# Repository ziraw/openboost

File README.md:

# Open Source Boost Controller w/ ESP32-C3 SuperMini.  
This is REV2.0 fixing the mistakes of my previous PCB design, it's currently not field tested. 

**The Code was mainly written by an LLM, since I'm extremely inexperienced with coding, please be advised that this is not in any way "safe" to hook up to your engine, please take a minute and review the code yourself and decide for yourself. If you find anything that you might want to change I'm more than happy to see a PR opened!**  
speaking of code, the 2 LEDs are currently not in use.

I'm grabbing the MAP signal off of my gauge atm, which seems to work perfectly fine. You can theoretically hook up a separate sensor to the board itself if you want, although I would never ever use any sort of boost controller without an actual gauge!  

### I/O
It has a 5V output and a sensor passthrough on the JST connector, alongside the main I/O;  
1 - 12V  
2 - GND  
3 - SENS I/O  
4 - SENS I/O  
5 - 5V  
6 - VALVE  

The controller sits between the Valves GND connection and the Chassis to switch it at ~28hz via a PWM signal generated by a PID controller running on the ESP32.
To set Parameters (PID and Boost) it runs a Webserver on it's own WIFI network, which is kind of tedious, but I might add physical controls too a future version, for now the aim of this project is to keep it as **cheap and accessible as possible.**

### BOM (THT unless Specified):
- ESP32-C3 SuperMini  
- IRLZ44N  
- TC4422  
- TIP2955  
- L7805  
- 6P JST-VH Horizontal Connector  
- 2x SMD 2020 WS2812B (not used in Code atm)  
- Various Resistors  
- 2x220uF 16V  
- 3x100nF Ceramic  
- 1N4007 Diode (at Boost Valve)  
- (Pin Sockets for ESP32)

Valve used at Wastegate: BMW N75 Boost Control Valve (on a CA18DET Engine), although any suitable boost/mac valve should be fine to use. You have to hook up above mentioned flyback diode directly to the pins of the valve.

Link to my original reddit post from rev 1: https://www.reddit.com/r/esp32/comments/1vrntt0/i_made_a_boost_controller_with_a_esp32c3_first/

### Schematics

Feel free to DM me on reddit: /u/ziraw_tech

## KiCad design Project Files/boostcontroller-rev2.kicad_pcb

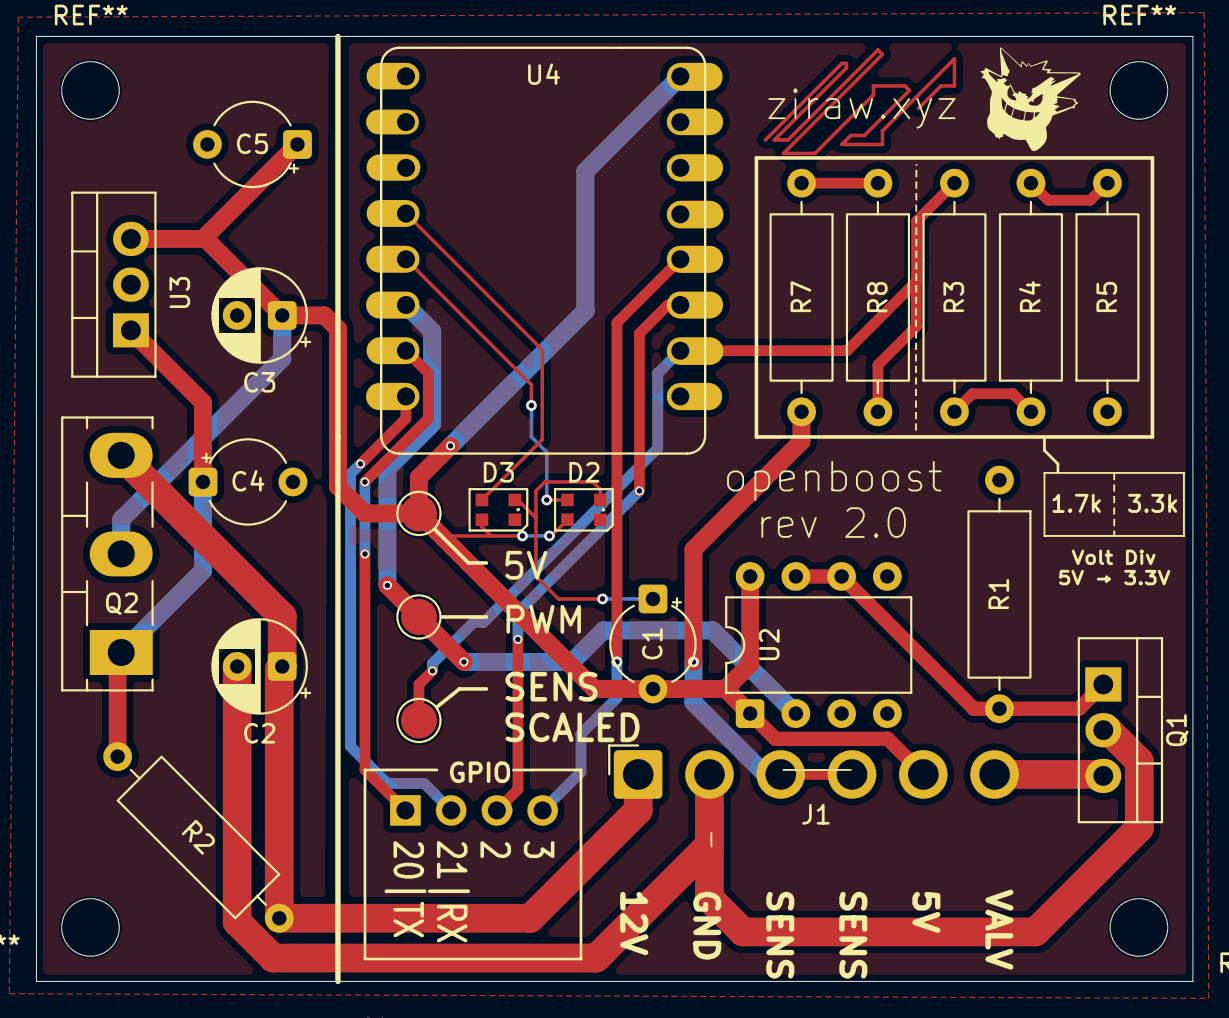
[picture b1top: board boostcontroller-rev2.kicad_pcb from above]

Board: 2 copper layers, 64.2 x 52.5 mm, 24 parts (0 on the bottom side), 18 nets.

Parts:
C1: Ceramic 100nF; CP_Radial_Tantal_D4.5mm_P5.00mm
C2, C3: 220uF 16V; CP_Radial_D5.0mm_P2.50mm
C4, C5: C 0.1uF; CP_Radial_Tantal_D4.5mm_P5.00mm
D2, D3: WS2812B; LED_WS2812B-2020_PLCC4_2.0x2.0mm
J1: Conn_01x06_Pin; JST_VH_B6PS-VH_1x06_P3.96mm_Horizontal
J2: Conn_01x04_Pin; PinHeader_1x04_P2.54mm_Vertical
Q1: IRLZ44N; TO-220-3_Vertical
Q2: TIP2955; TO-218-3_Vertical
R1: R10k; R_Axial_DIN0309_L9.0mm_D3.2mm_P12.70mm_Horizontal
R2: R3.3Ohm; R_Axial_DIN0309_L9.0mm_D3.2mm_P12.70mm_Horizontal
R3, R4, R5, R7, R8: R_Axial_DIN0309_L9.0mm_D3.2mm_P12.70mm_Horizontal
TP1, TP2, TP3: TestPoint; TestPoint_Pad_D2.0mm
U2: TC4422; DIP-8_W7.62mm
U3: L7805; TO-220-3_Vertical
U4: ESP32-C3-SuperMini; ESP32-S3-SuperMini

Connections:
+12V: C2.1, J1.1, Q2.3 (E), R2.1
/5V_bus: C1.2, C3.1, C5.1, D2.2 (VDD), D3.2 (VDD), J1.5, Q2.2 (C), TP1.1 (1_1), U2.1 (VDD), U2.8 (VDD), U3.3 (OUT), U4.5V (5_V)
/R_array_1.7k_out: R3.2, R8.2, TP2.1 (1_1), U4.1 (GPIO1)
/R_array_in: J1.3, J1.4, R7.2
GND: C1.1, C2.2, C3.2, C4.2, C5.2, D2.3 (VSS), D3.3 (VSS), J1.2, Q1.2 (D), R1.2, R5.1, U2.4 (GND), U2.5 (GND), U3.2 (GND), U4.GND
unnamed: D2.4 (DIN), U4.9 (GPIO9)
unnamed: D3.4 (DIN), U4.8 (GPIO8)
unnamed: J1.6, Q1.3 (S)
unnamed: J2.1, U4.20 (GPIO20)
unnamed: J2.2, U4.21 (GPIO21)
unnamed: J2.3, U4.2 (GPIO2)
unnamed: J2.4, U4.3 (GPIO3)
unnamed: Q1.1 (G), R1.1, U2.6 (OUTPUT), U2.7 (OUTPUT)
unnamed: C4.1, Q2.1 (B), R2.2, U3.1 (IN)
unnamed: R3.1, R4.1
unnamed: R4.2, R5.2
unnamed: R7.1, R8.1
unnamed: TP3.1 (1_1), U2.2 (INPUT), U4.10 (GPIO10)
